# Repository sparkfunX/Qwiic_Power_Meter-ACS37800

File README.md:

SparkX Power Meter - ACS37800 (Qwiic)
===================================================

[*SparkX Power Meter - ACS37800 (Qwiic) (SPX-17873)*](https://www.sparkfun.com/products/17873)

Need a power sensor that can sense voltage up to 60VDC and current up to 30A? This is the product for you!

The Allegro MicroSystems ACS37800 power monitoring IC greatly simplifies the addition of power monitoring to many powered systems and is ideal for
heavy current applications like:
- Monitoring the power drawn by a 3D-printer
- Monitoring the power drawn from a UAV battery
- Battery charging / conditioning
- Solar / photovoltaic panel power monitoring

Allegro’s Hall-effect-based, galvanically isolated current sensing technology achieves reinforced isolation ratings in a small PCB footprint.
These features enable isolated current sensing without expensive Rogowski coils, oversized current transformers, isolated operational amplifiers,
or the power loss of shunt resistors.

The ACS37800 power monitoring IC offers key power measurement parameters that can easily be accessed through its digital interface. Dedicated and
configurable I/O pins for voltage/current zero crossing, undervoltage and overvoltage reporting, and fast overcurrent fault detection are available.
User configuration of the IC is available through on-chip EEPROM.

Important Note
-------------------
This product is not suitable for low current applications due to the +/-0.1A RMS Noise on the current channel.

Sensing less than an Amp? This is _not_ the product for you...

Safety Information
-------------------
**Although the ACS37800 power monitoring IC is capable of monitoring AC power at high line voltages, the SparkX Power Meter is designed for
Safety Extra Low Voltage (SELV) applications of up to 60VDC only. Its use in AC power systems is _not_ recommended.**

Repository Contents
-------------------
* **/Documents** - datasheets etc.
* **/Hardware** - Eagle design files (.brd, .sch)
* **/Production_Test** - production test code (.ino) - run this in the Arduino IDE
* **LICENSE.md** - license information

Documentation
--------------
* **[ACS37800 Arduino Library](https://github.com/sparkfun/SparkFun_ACS37800_Power_Monitor_Arduino_Library)** - Arduino library for the SparkFun Power Meter - ACS37800.
* **[DRAFT Hookup Guide](./HOOKUP.md)** - Basic hookup guide for the SparkX Power Meter - ACS37800.

Product Versions
----------------
* [SPX-17873](https://www.sparkfun.com/products/17873) - Original SparkX Release.

License Information
-------------------

This product is _**open source**_!

Please review the LICENSE.md file for license information.

If you have any questions or concerns on licensing, please contact technical support on our [SparkFun forums](https://forum.sparkfun.com/viewforum.php?f=123).

Distributed as-is; no warranty is given.

- Your friends at SparkFun.

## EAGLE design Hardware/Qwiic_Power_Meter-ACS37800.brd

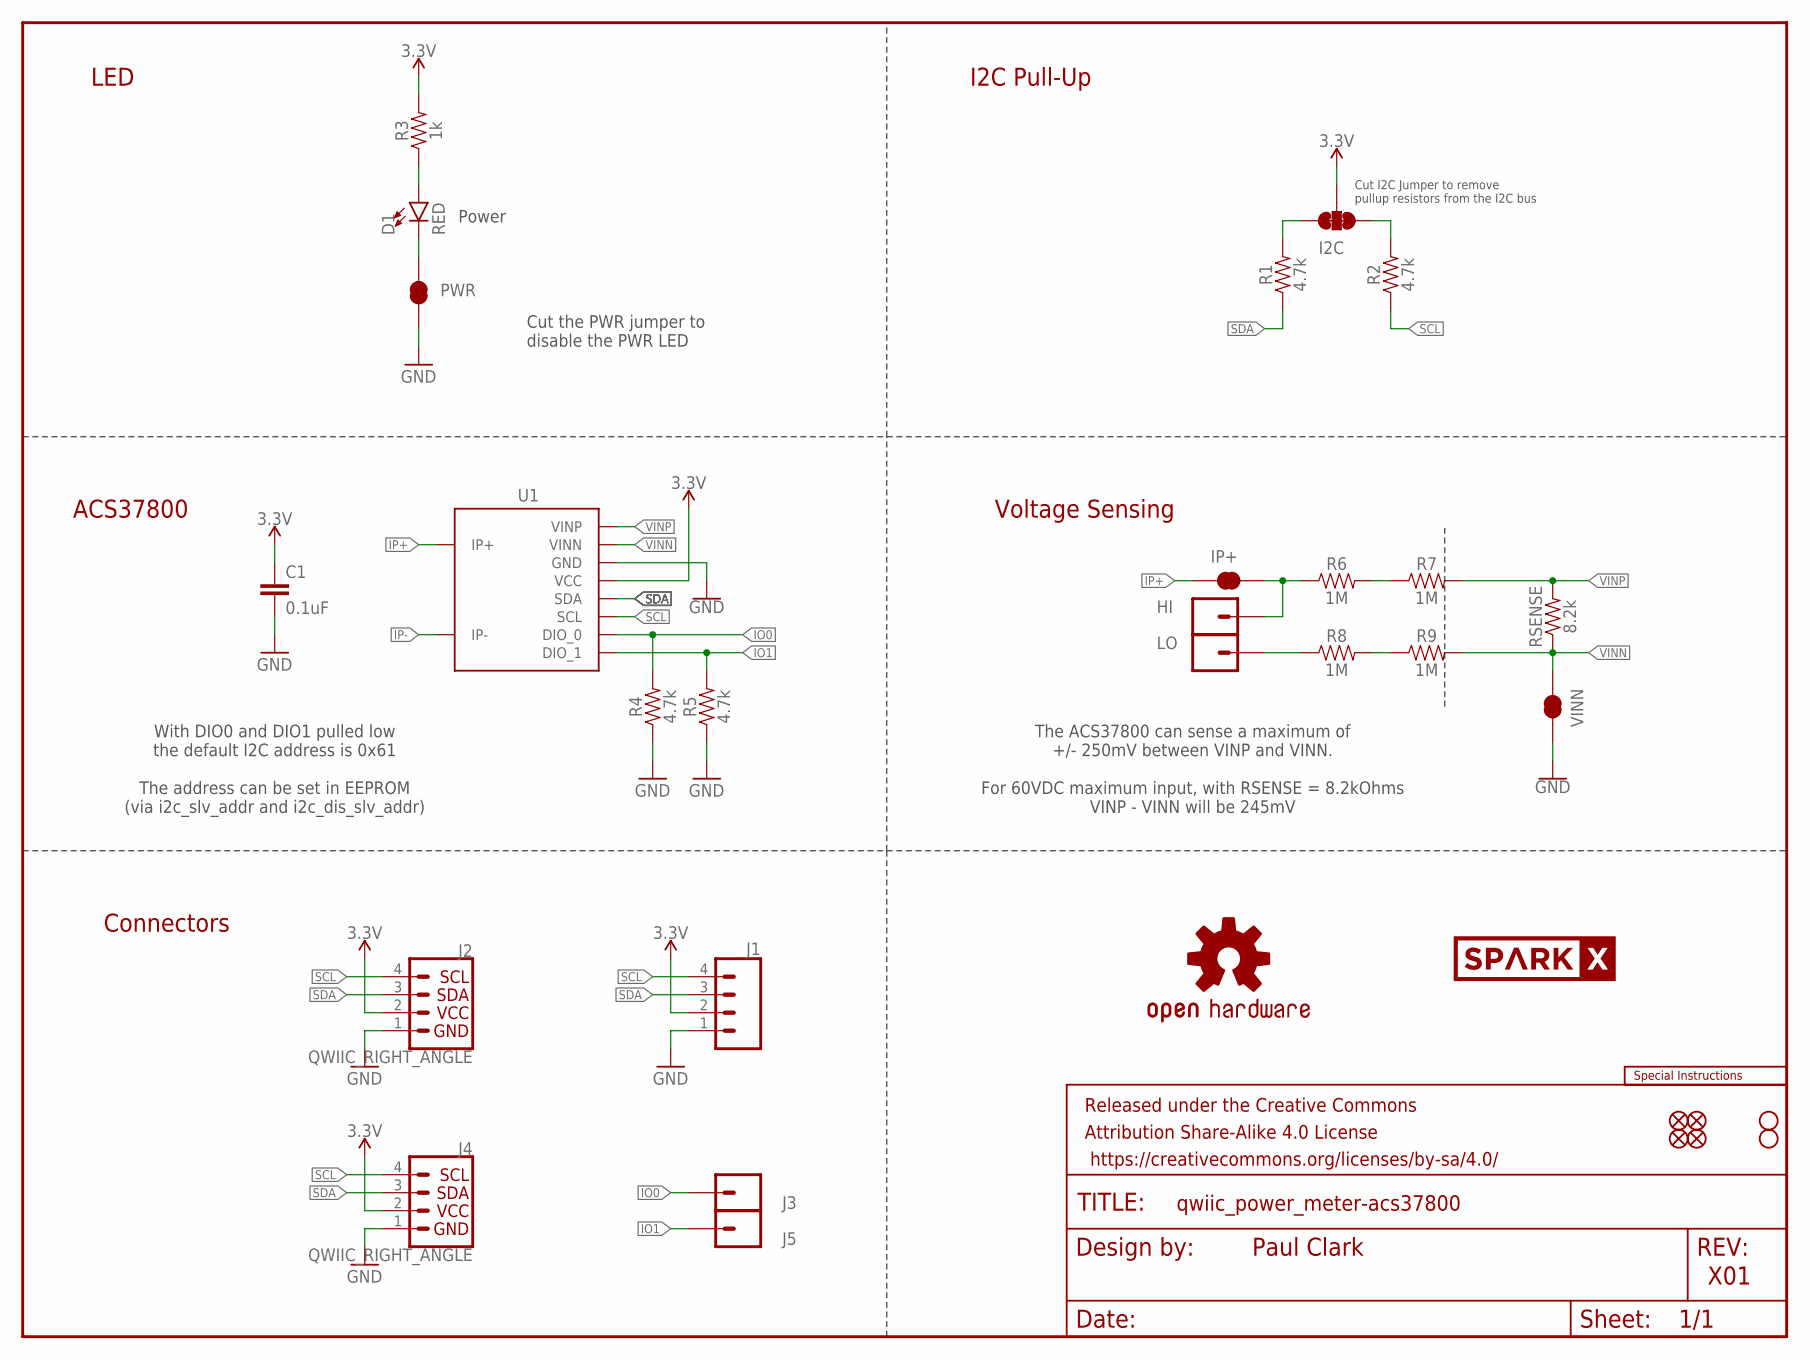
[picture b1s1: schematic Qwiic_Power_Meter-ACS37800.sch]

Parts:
C1: 0.1uF; 0603
D1: RED; LED-0603
FRAME1: FRAME-LETTER; CREATIVE_COMMONS
HI: CONN_01PTH_NO_SILK_YES_STOP; 1X01_NO_SILK
I2C: JUMPER-SMT_3_2-NC_TRACE_SILK; SMT-JUMPER_3_2-NC_TRACE_SILK
IP+: JUMPER-SMT_2_NC_TRACE_SILK; SMT-JUMPER_2_NC_TRACE_SILK
J1: CONN_041X04_NO_SILK; 1X04_NO_SILK
J2, J4: QWIIC_RIGHT_ANGLE; JST04_1MM_RA
J3, J5: CONN_01PTH_NO_SILK_YES_STOP; 1X01_NO_SILK
JP1, JP2, JP5, JP6: FIDUCIALUFIDUCIAL; MICRO-FIDUCIAL
JP3, JP4: STAND-OFF
LO: CONN_01PTH_NO_SILK_YES_STOP; 1X01_NO_SILK
LOGO1: SPECIAL_INSTRUCTIONS-ORDERING; ORDERING_INSTRUCTIONS
LOGO5: OSHW-LOGOS; OSHW-LOGO-S
PWR: JUMPER-SMT_2_NC_TRACE_SILK; SMT-JUMPER_2_NC_TRACE_SILK
R1, R2, R4, R5: 4.7k; 0603
R3: 1k; 0603
R6, R7, R8, R9: 1M; 0603
RSENSE: 8.2k; 0603
U1: ACS37800; ACS37800_THROUGH_HOLE
U$18: SPARKX-LOGO3; SPARKX-SMALL
VINN: JUMPER-SMT_2_NC_TRACE_SILK; SMT-JUMPER_2_NC_TRACE_SILK

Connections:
3.3V: C1.1, I2C.2, J1.2, J2.2, J4.2, R3.2, U1.13 (VCC)
GND: C1.2, J1.1, J2.1, J4.1, PWR.1, R4.1, R5.1, U1.14 (GND), VINN.2
HI: HI.1, IP+.2, R6.1
IO0: J3.1, R4.2, U1.10 (DIO_0)
IO1: J5.1, R5.2, U1.9 (DIO_1)
IP+: IP+.1, U1.1 (IP+), U1.2 (IP+), U1.3 (IP+), U1.4 (IP+), U1.CIN1 (IP+), U1.CIN2 (IP+), U1.CIN3 (IP+), U1.CIN4 (IP+), U1.CIN5 (IP+), U1.CIN6 (IP+), U1.CIN7 (IP+), U1.CIN8 (IP+), U1.CIN9 (IP+), U1.CIN10 (IP+), U1.CIN11 (IP+), U1.CIN12 (IP+), U1.CIN13 (IP+), U1.CIN14 (IP+), U1.CIN15 (IP+), U1.CIN16 (IP+), U1.CIN17 (IP+), U1.CIN18 (IP+), U1.CIN19 (IP+), U1.CIN20 (IP+), U1.CIN21 (IP+), U1.CIN22 (IP+), U1.CIN23 (IP+), U1.CIN24 (IP+), U1.CIN25 (IP+), U1.CIN26 (IP+), U1.CIN27 (IP+), U1.CIN28 (IP+), U1.CIN29 (IP+), U1.CIN30 (IP+), U1.CIN31 (IP+), U1.CIN32 (IP+), U1.CIN33 (IP+), U1.CIN34 (IP+), U1.CIN35 (IP+), U1.CIN36 (IP+), U1.C_IN (IP+), U1.C_IN_BREAKOUT (IP+)
IP-: U1.5 (IP-), U1.6 (IP-), U1.7 (IP-), U1.8 (IP-), U1.COUT1 (IP-), U1.COUT2 (IP-), U1.COUT3 (IP-), U1.COUT4 (IP-), U1.COUT5 (IP-), U1.COUT6 (IP-), U1.COUT7 (IP-), U1.COUT8 (IP-), U1.COUT9 (IP-), U1.COUT10 (IP-), U1.COUT11 (IP-), U1.COUT12 (IP-), U1.COUT13 (IP-), U1.COUT14 (IP-), U1.COUT15 (IP-), U1.COUT16 (IP-), U1.COUT17 (IP-), U1.COUT18 (IP-), U1.COUT19 (IP-), U1.COUT20 (IP-), U1.COUT21 (IP-), U1.COUT22 (IP-), U1.COUT23 (IP-), U1.COUT24 (IP-), U1.COUT25 (IP-), U1.COUT26 (IP-), U1.COUT27 (IP-), U1.COUT28 (IP-), U1.COUT29 (IP-), U1.COUT30 (IP-), U1.COUT31 (IP-), U1.COUT32 (IP-), U1.COUT33 (IP-), U1.COUT34 (IP-), U1.COUT35 (IP-), U1.COUT36 (IP-), U1.C_OUT (IP-), U1.C_OUT_BREAKOUT (IP-)
unnamed: D1.C, PWR.2
unnamed: I2C.3, R1.2
unnamed: D1.A, R3.1
unnamed: I2C.1, R2.2
unnamed: R6.2, R7.1
unnamed: R8.2, R9.1
unnamed: LO.1, R8.1
SCL: J1.4, J2.4, J4.4, R2.1, U1.11 (SCL)
SDA: J1.3, J2.3, J4.3, R1.1, U1.12 (SDA)
VINN: R9.2, RSENSE.1, U1.15 (VINN), VINN.1
VINP: R7.2, RSENSE.2, U1.16 (VINP)

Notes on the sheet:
Paul Clark
X01
Power
I2C Pull-Up
ACS37800
Connectors
Cut the PWR jumper to disable the PWR LED
Cut I2C Jumper to remove pullup resistors from the I2C bus
LED
Voltage Sensing
With DIO0 and DIO1 pulled low the default I2C address is 0x61 The address can be set in EEPROM (via i2c_slv_addr and i2c_dis_slv_addr)
The ACS37800 can sense a maximum of +/- 250mV between VINP and VINN. For 60VDC maximum input, with RSENSE = 8.2kOhms VINP - VINN will be 245mV

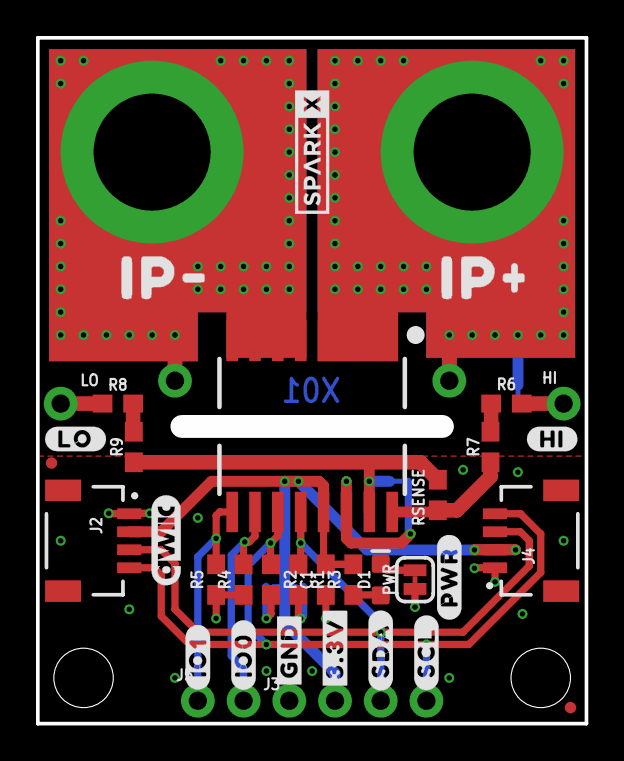
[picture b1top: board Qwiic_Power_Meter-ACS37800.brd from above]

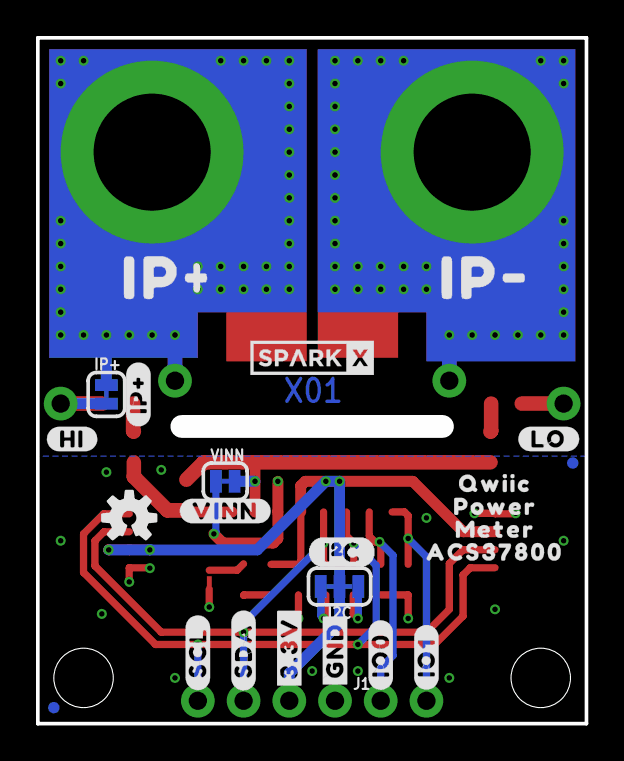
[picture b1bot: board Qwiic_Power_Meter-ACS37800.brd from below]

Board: 4 copper layers, 29.4 x 37.0 mm, 64 parts (25 on the bottom side), 18 nets.

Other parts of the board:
U$1, U$33: #GND#0
U$2, U$34: #3#3V#0
U$3, U$35: #SDA#0
U$4, U$36: #SCL#0
U$5, U$6: #IO0#0
U$7, U$8: #IO1#0
U$9, U$10, U$11, U$12: IP#0
U$13, U$14: #HI#0
U$15: I2C
U$16: QWIIC_5MM
U$17, U$19: #LO#0
U$20: SPARKX-LOGO3; SPARKX-SMALL
U$21: #VINN#0
U$22: #IP##0
U$23: ACS378000
U$24: METER0
U$25: POWER0
U$26: QWIIC0
U$32: #PWR#0

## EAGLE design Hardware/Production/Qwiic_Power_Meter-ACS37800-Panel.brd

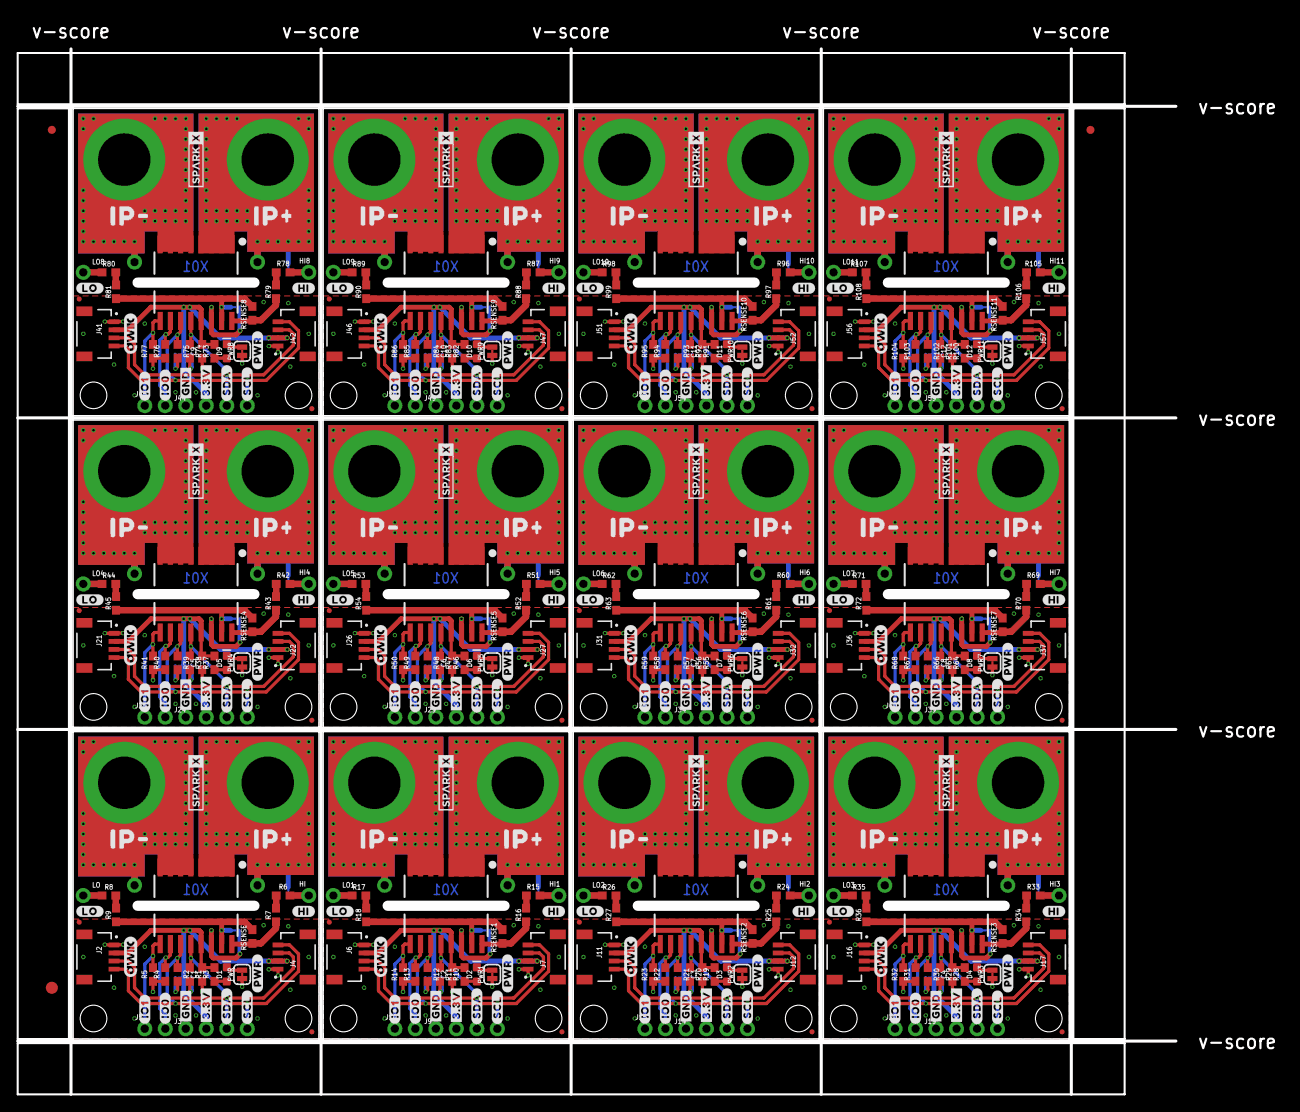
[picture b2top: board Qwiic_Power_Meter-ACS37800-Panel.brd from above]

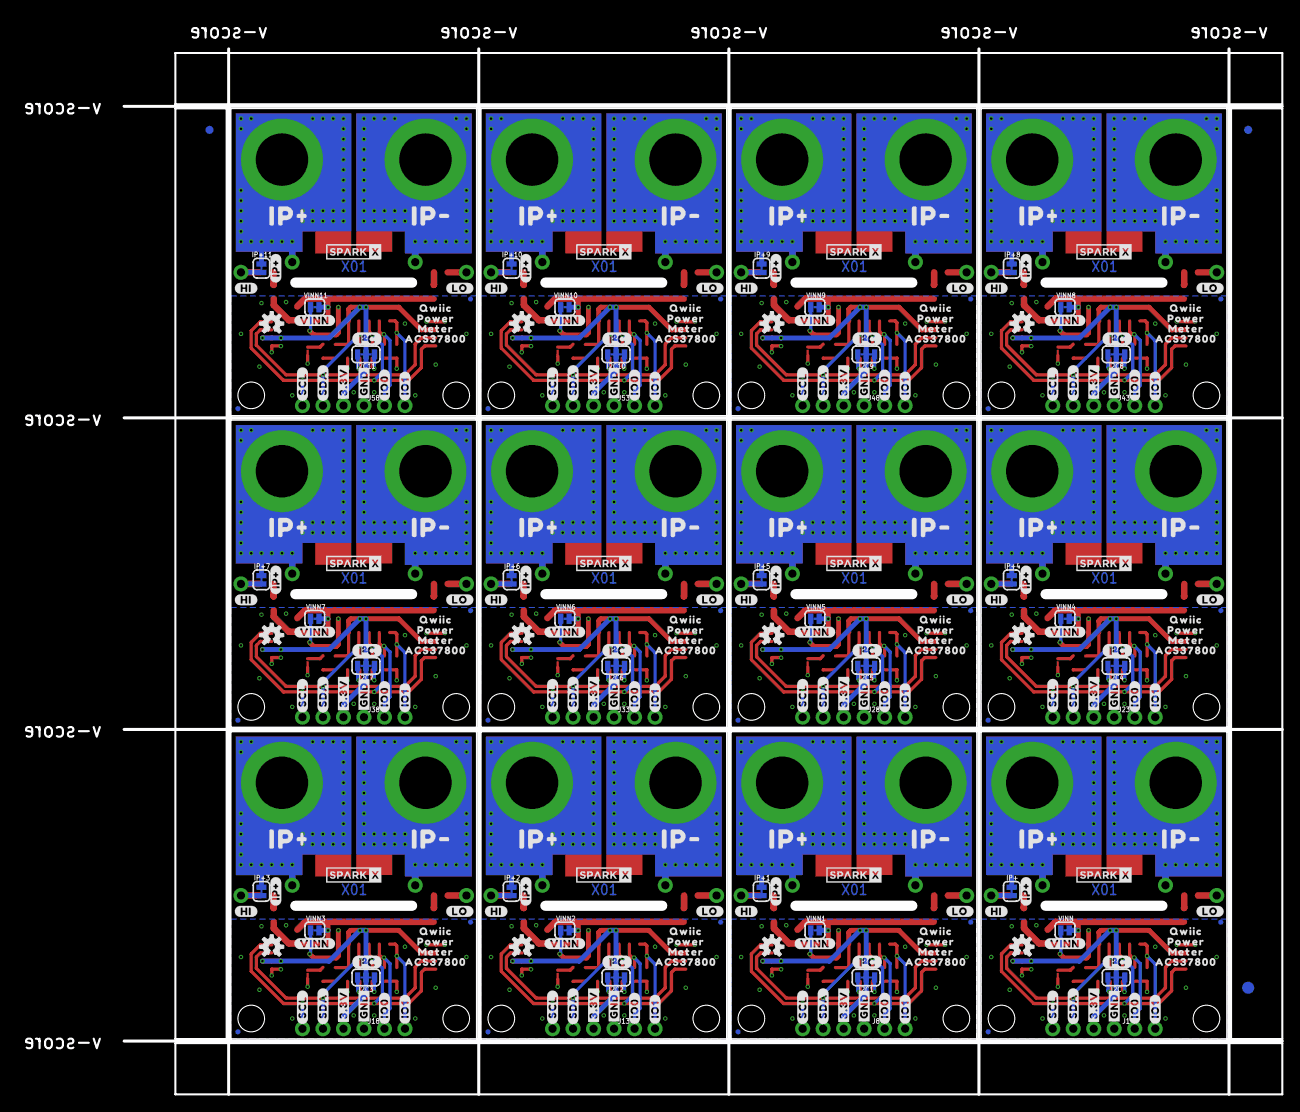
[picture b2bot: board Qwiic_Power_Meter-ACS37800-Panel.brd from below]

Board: 4 copper layers, 155.8 x 132.5 mm, 750 parts (303 on the bottom side), 216 nets.

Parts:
C1, C2, C3, C4, C5, C6, C7, C8, C9, C10, C11, C12: 0.1uF; 0603
D1, D2, D3, D4, D5, D6, D7, D8, D9, D10, D11, D12: RED; LED-0603
E$1, E$2, E$3, E$4: FIDUCIAL-1X2
E$5, E$6: FIDUCIAL-1.5X3
HI, HI1, HI2, HI3, HI4, HI5, HI6, HI7, HI8, HI9, HI10, HI11: 1X01_NO_SILK
I2C, I2C1, I2C2, I2C3, I2C4, I2C5, I2C6, I2C7, I2C8, I2C9, I2C10, I2C11: JUMPER-SMT_3_2-NC_TRACE_SILK; SMT-JUMPER_3_2-NC_TRACE_SILK
IP+, IP+1, IP+2, IP+3, IP+4, IP+5, IP+6, IP+7, IP+8, IP+9, IP+10, IP+11: JUMPER-SMT_2_NC_TRACE_SILK; SMT-JUMPER_2_NC_TRACE_SILK
J1, J8, J13, J18, J23, J28, J33, J38, J43, J48, J53, J58: 1X04_NO_SILK
J2, J4, J6, J7, J11, J12, J16, J17, J21, J22, J26, J27, J31, J32, J36, J37, J41, J42, J46, J47, J51, J52, J56, J57: QWIIC_RIGHT_ANGLE; JST04_1MM_RA
J3, J5, J9, J10, J14, J15, J19, J20, J24, J25, J29, J30, J34, J35, J39, J40, J44, J45, J49, J50, J54, J55, J59, J60: 1X01_NO_SILK
JP1, JP2, JP5, JP6, JP9, JP10, JP11, JP12, JP15, JP16, JP17, JP18, JP21, JP22, JP23, JP24, JP27, JP28, JP29, JP30, JP33, JP34, JP35, JP36, JP39, JP40, JP41, JP42, JP45, JP46, JP47, JP48, JP51, JP52, JP53, JP54, JP57, JP58, JP59, JP60, JP63, JP64, JP65, JP66, JP69, JP70, JP71, JP72: FIDUCIALUFIDUCIAL; MICRO-FIDUCIAL
JP3, JP4, JP7, JP8, JP13, JP14, JP19, JP20, JP25, JP26, JP31, JP32, JP37, JP38, JP43, JP44, JP49, JP50, JP55, JP56, JP61, JP62, JP67, JP68: STAND-OFF
LO, LO1, LO2, LO3, LO4, LO5, LO6, LO7, LO8, LO9, LO10, LO11: 1X01_NO_SILK
LOGO1, LOGO2, LOGO3, LOGO4, LOGO5, LOGO6, LOGO7, LOGO8, LOGO9, LOGO10, LOGO11, LOGO12: OSHW-LOGOS; OSHW-LOGO-S
PWR, PWR1, PWR2, PWR3, PWR4, PWR5, PWR6, PWR7, PWR8, PWR9, PWR10, PWR11: JUMPER-SMT_2_NC_TRACE_SILK; SMT-JUMPER_2_NC_TRACE_SILK
R1, R2, R4, R5, R11, R12, R13, R14, R20, R21, R22, R23, R29, R30, R31, R32, R38, R39, R40, R41, R47, R48, R49, R50, R56, R57, R58, R59, R65, R66, R67, R68, R74, R75, R76, R77, R83, R84, R85, R86, R92, R93, R94, R95, R101, R102, R103, R104: 4.7k; 0603
R3, R10, R19, R28, R37, R46, R55, R64, R73, R82, R91, R100: 1k; 0603
R6, R7, R8, R9, R15, R16, R17, R18, R24, R25, R26, R27, R33, R34, R35, R36, R42, R43, R44, R45, R51, R52, R53, R54, R60, R61, R62, R63, R69, R70, R71, R72, R78, R79, R80, R81, R87, R88, R89, R90, R96, R97, R98, R99, R105, R106, R107, R108: 1M; 0603
RSENSE, RSENSE1, RSENSE2, RSENSE3, RSENSE4, RSENSE5, RSENSE6, RSENSE7, RSENSE8, RSENSE9, RSENSE10, RSENSE11: 8.2k; 0603
U1, U2, U3, U4, U5, U6, U7, U8, U9, U10, U11, U12: ACS37800_THROUGH_HOLE
U$1, U$31, U$33, U$40, U$67, U$71, U$98, U$102, U$129, U$133, U$160, U$164, U$191, U$195, U$222, U$226, U$253, U$257, U$284, U$288, U$315, U$319, U$346, U$350: #GND#0
U$2, U$34, U$37, U$41, U$68, U$72, U$99, U$103, U$130, U$134, U$161, U$165, U$192, U$196, U$223, U$227, U$254, U$258, U$285, U$289, U$316, U$320, U$347, U$351: #3#3V#0
U$3, U$35, U$38, U$42, U$69, U$73, U$100, U$104, U$131, U$135, U$162, U$166, U$193, U$197, U$224, U$228, U$255, U$259, U$286, U$290, U$317, U$321, U$348, U$352: #SDA#0
U$4, U$36, U$39, U$43, U$70, U$74, U$101, U$105, U$132, U$136, U$163, U$167, U$194, U$198, U$225, U$229, U$256, U$260, U$287, U$291, U$318, U$322, U$349, U$353: #SCL#0
U$5, U$6, U$59, U$60, U$90, U$91, U$121, U$122, U$152, U$153, U$183, U$184, U$214, U$215, U$245, U$246, U$276, U$277, U$307, U$308, U$338, U$339, U$369, U$370: #IO0#0
U$7, U$8, U$61, U$62, U$92, U$93, U$123, U$124, U$154, U$155, U$185, U$186, U$216, U$217, U$247, U$248, U$278, U$279, U$309, U$310, U$340, U$341, U$371, U$372: #IO1#0
U$9, U$10, U$11, U$12, U$45, U$46, U$47, U$48, U$76, U$77, U$78, U$79, U$107, U$108, U$109, U$110, U$138, U$139, U$140, U$141, U$169, U$170, U$171, U$172, U$200, U$201, U$202, U$203, U$231, U$232, U$233, U$234, U$262, U$263, U$264, U$265, U$293, U$294, U$295, U$296, U$324, U$325, U$326, U$327, U$355, U$356, U$357, U$358: IP#0
U$13, U$14, U$49, U$50, U$80, U$81, U$111, U$112, U$142, U$143, U$173, U$174, U$204, U$205, U$235, U$236, U$266, U$267, U$297, U$298, U$328, U$329, U$359, U$360: #HI#0
U$15, U$27, U$63, U$94, U$125, U$156, U$187, U$218, U$249, U$280, U$311, U$342: I2C
U$16, U$28, U$64, U$95, U$126, U$157, U$188, U$219, U$250, U$281, U$312, U$343: QWIIC_5MM
U$17, U$19, U$51, U$52, U$82, U$83, U$113, U$114, U$144, U$145, U$175, U$176, U$206, U$207, U$237, U$238, U$268, U$269, U$299, U$300, U$330, U$331, U$361, U$362: #LO#0
U$18, U$20, U$29, U$44, U$65, U$75, U$96, U$106, U$127, U$137, U$158, U$168, U$189, U$199, U$220, U$230, U$251, U$261, U$282, U$292, U$313, U$323, U$344, U$354: SPARKX-LOGO3; SPARKX-SMALL
U$21, U$53, U$84, U$115, U$146, U$177, U$208, U$239, U$270, U$301, U$332, U$363: #VINN#0
U$22, U$54, U$85, U$116, U$147, U$178, U$209, U$240, U$271, U$302, U$333, U$364: #IP##0
U$23, U$55, U$86, U$117, U$148, U$179, U$210, U$241, U$272, U$303, U$334, U$365: ACS378000
U$24, U$56, U$87, U$118, U$149, U$180, U$211, U$242, U$273, U$304, U$335, U$366: METER0
U$25, U$57, U$88, U$119, U$150, U$181, U$212, U$243, U$274, U$305, U$336, U$367: POWER0
U$26, U$58, U$89, U$120, U$151, U$182, U$213, U$244, U$275, U$306, U$337, U$368: QWIIC0
U$30, U$32, U$66, U$97, U$128, U$159, U$190, U$221, U$252, U$283, U$314, U$345: #PWR#0
VINN, VINN1, VINN2, VINN3, VINN4, VINN5, VINN6, VINN7, VINN8, VINN9, VINN10, VINN11: JUMPER-SMT_2_NC_TRACE_SILK; SMT-JUMPER_2_NC_TRACE_SILK

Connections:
3.3V: C1.1, I2C.2, J1.2, J2.2, J4.2, R3.2, U1.13
3.3V1: C2.1, I2C1.2, J6.2, J7.2, J8.2, R10.2, U2.13
3.3V2: C3.1, I2C2.2, J11.2, J12.2, J13.2, R19.2, U3.13
3.3V3: C4.1, I2C3.2, J16.2, J17.2, J18.2, R28.2, U4.13
3.3V4: C5.1, I2C4.2, J21.2, J22.2, J23.2, R37.2, U5.13
3.3V5: C6.1, I2C5.2, J26.2, J27.2, J28.2, R46.2, U6.13
3.3V6: C7.1, I2C6.2, J31.2, J32.2, J33.2, R55.2, U7.13
3.3V7: C8.1, I2C7.2, J36.2, J37.2, J38.2, R64.2, U8.13
3.3V8: C9.1, I2C8.2, J41.2, J42.2, J43.2, R73.2, U9.13
3.3V9: C10.1, I2C9.2, J46.2, J47.2, J48.2, R82.2, U10.13
3.3V10: C11.1, I2C10.2, J51.2, J52.2, J53.2, R91.2, U11.13
3.3V11: C12.1, I2C11.2, J56.2, J57.2, J58.2, R100.2, U12.13
GND: C1.2, J1.1, J2.1, J4.1, PWR.1, R4.1, R5.1, U1.14, VINN.2
GND1: C2.2, J6.1, J7.1, J8.1, PWR1.1, R13.1, R14.1, U2.14, VINN1.2
GND2: C3.2, J11.1, J12.1, J13.1, PWR2.1, R22.1, R23.1, U3.14, VINN2.2
GND3: C4.2, J16.1, J17.1, J18.1, PWR3.1, R31.1, R32.1, U4.14, VINN3.2
GND4: C5.2, J21.1, J22.1, J23.1, PWR4.1, R40.1, R41.1, U5.14, VINN4.2
GND5: C6.2, J26.1, J27.1, J28.1, PWR5.1, R49.1, R50.1, U6.14, VINN5.2
GND6: C7.2, J31.1, J32.1, J33.1, PWR6.1, R58.1, R59.1, U7.14, VINN6.2
GND7: C8.2, J36.1, J37.1, J38.1, PWR7.1, R67.1, R68.1, U8.14, VINN7.2
GND8: C9.2, J41.1, J42.1, J43.1, PWR8.1, R76.1, R77.1, U9.14, VINN8.2
GND9: C10.2, J46.1, J47.1, J48.1, PWR9.1, R85.1, R86.1, U10.14, VINN9.2
GND10: C11.2, J51.1, J52.1, J53.1, PWR10.1, R94.1, R95.1, U11.14, VINN10.2
GND11: C12.2, J56.1, J57.1, J58.1, PWR11.1, R103.1, R104.1, U12.14, VINN11.2
HI: HI.1, IP+.2, R6.1
HI1: HI1.1, IP+1.2, R15.1
HI2: HI2.1, IP+2.2, R24.1
HI3: HI3.1, IP+3.2, R33.1
HI4: HI4.1, IP+4.2, R42.1
HI5: HI5.1, IP+5.2, R51.1
HI6: HI6.1, IP+6.2, R60.1
HI7: HI7.1, IP+7.2, R69.1
HI8: HI8.1, IP+8.2, R78.1
HI9: HI9.1, IP+9.2, R87.1
HI10: HI10.1, IP+10.2, R96.1
HI11: HI11.1, IP+11.2, R105.1
IO0: J3.1, R4.2, U1.10
IO1: J5.1, R5.2, U1.9
IO2: J9.1, R13.2, U2.10
IO3: J10.1, R14.2, U2.9
IO4: J14.1, R22.2, U3.10
IO5: J15.1, R23.2, U3.9
IO6: J19.1, R31.2, U4.10
IO7: J20.1, R32.2, U4.9
IO8: J24.1, R40.2, U5.10
IO9: J25.1, R41.2, U5.9
IO10: J29.1, R49.2, U6.10
IO11: J30.1, R50.2, U6.9
IO12: J34.1, R58.2, U7.10
IO13: J35.1, R59.2, U7.9
IO14: J39.1, R67.2, U8.10
IO15: J40.1, R68.2, U8.9
IO16: J44.1, R76.2, U9.10
IO17: J45.1, R77.2, U9.9
IO18: J49.1, R85.2, U10.10
IO19: J50.1, R86.2, U10.9
IO20: J54.1, R94.2, U11.10
IO21: J55.1, R95.2, U11.9
IO22: J59.1, R103.2, U12.10
IO23: J60.1, R104.2, U12.9
IP+: IP+.1, U1.1, U1.2, U1.3, U1.4, U1.CIN1, U1.CIN2, U1.CIN3, U1.CIN4, U1.CIN5, U1.CIN6, U1.CIN7, U1.CIN8, U1.CIN9, U1.CIN10, U1.CIN11, U1.CIN12, U1.CIN13, U1.CIN14, U1.CIN15, U1.CIN16, U1.CIN17, U1.CIN18, U1.CIN19, U1.CIN20, U1.CIN21, U1.CIN22, U1.CIN23, U1.CIN24, U1.CIN25, U1.CIN26, U1.CIN27, U1.CIN28, U1.CIN29, U1.CIN30, U1.CIN31, U1.CIN32, U1.CIN33, U1.CIN34, U1.CIN35, U1.CIN36, U1.C_IN, U1.C_IN_BREAKOUT
IP+1: IP+1.1, U2.1, U2.2, U2.3, U2.4, U2.CIN1, U2.CIN2, U2.CIN3, U2.CIN4, U2.CIN5, U2.CIN6, U2.CIN7, U2.CIN8, U2.CIN9, U2.CIN10, U2.CIN11, U2.CIN12, U2.CIN13, U2.CIN14, U2.CIN15, U2.CIN16, U2.CIN17, U2.CIN18, U2.CIN19, U2.CIN20, U2.CIN21, U2.CIN22, U2.CIN23, U2.CIN24, U2.CIN25, U2.CIN26, U2.CIN27, U2.CIN28, U2.CIN29, U2.CIN30, U2.CIN31, U2.CIN32, U2.CIN33, U2.CIN34, U2.CIN35, U2.CIN36, U2.C_IN, U2.C_IN_BREAKOUT
IP+2: IP+2.1, U3.1, U3.2, U3.3, U3.4, U3.CIN1, U3.CIN2, U3.CIN3, U3.CIN4, U3.CIN5, U3.CIN6, U3.CIN7, U3.CIN8, U3.CIN9, U3.CIN10, U3.CIN11, U3.CIN12, U3.CIN13, U3.CIN14, U3.CIN15, U3.CIN16, U3.CIN17, U3.CIN18, U3.CIN19, U3.CIN20, U3.CIN21, U3.CIN22, U3.CIN23, U3.CIN24, U3.CIN25, U3.CIN26, U3.CIN27, U3.CIN28, U3.CIN29, U3.CIN30, U3.CIN31, U3.CIN32, U3.CIN33, U3.CIN34, U3.CIN35, U3.CIN36, U3.C_IN, U3.C_IN_BREAKOUT
IP+3: IP+3.1, U4.1, U4.2, U4.3, U4.4, U4.CIN1, U4.CIN2, U4.CIN3, U4.CIN4, U4.CIN5, U4.CIN6, U4.CIN7, U4.CIN8, U4.CIN9, U4.CIN10, U4.CIN11, U4.CIN12, U4.CIN13, U4.CIN14, U4.CIN15, U4.CIN16, U4.CIN17, U4.CIN18, U4.CIN19, U4.CIN20, U4.CIN21, U4.CIN22, U4.CIN23, U4.CIN24, U4.CIN25, U4.CIN26, U4.CIN27, U4.CIN28, U4.CIN29, U4.CIN30, U4.CIN31, U4.CIN32, U4.CIN33, U4.CIN34, U4.CIN35, U4.CIN36, U4.C_IN, U4.C_IN_BREAKOUT
IP+4: IP+4.1, U5.1, U5.2, U5.3, U5.4, U5.CIN1, U5.CIN2, U5.CIN3, U5.CIN4, U5.CIN5, U5.CIN6, U5.CIN7, U5.CIN8, U5.CIN9, U5.CIN10, U5.CIN11, U5.CIN12, U5.CIN13, U5.CIN14, U5.CIN15, U5.CIN16, U5.CIN17, U5.CIN18, U5.CIN19, U5.CIN20, U5.CIN21, U5.CIN22, U5.CIN23, U5.CIN24, U5.CIN25, U5.CIN26, U5.CIN27, U5.CIN28, U5.CIN29, U5.CIN30, U5.CIN31, U5.CIN32, U5.CIN33, U5.CIN34, U5.CIN35, U5.CIN36, U5.C_IN, U5.C_IN_BREAKOUT
IP+5: IP+5.1, U6.1, U6.2, U6.3, U6.4, U6.CIN1, U6.CIN2, U6.CIN3, U6.CIN4, U6.CIN5, U6.CIN6, U6.CIN7, U6.CIN8, U6.CIN9, U6.CIN10, U6.CIN11, U6.CIN12, U6.CIN13, U6.CIN14, U6.CIN15, U6.CIN16, U6.CIN17, U6.CIN18, U6.CIN19, U6.CIN20, U6.CIN21, U6.CIN22, U6.CIN23, U6.CIN24, U6.CIN25, U6.CIN26, U6.CIN27, U6.CIN28, U6.CIN29, U6.CIN30, U6.CIN31, U6.CIN32, U6.CIN33, U6.CIN34, U6.CIN35, U6.CIN36, U6.C_IN, U6.C_IN_BREAKOUT
IP+6: IP+6.1, U7.1, U7.2, U7.3, U7.4, U7.CIN1, U7.CIN2, U7.CIN3, U7.CIN4, U7.CIN5, U7.CIN6, U7.CIN7, U7.CIN8, U7.CIN9, U7.CIN10, U7.CIN11, U7.CIN12, U7.CIN13, U7.CIN14, U7.CIN15, U7.CIN16, U7.CIN17, U7.CIN18, U7.CIN19, U7.CIN20, U7.CIN21, U7.CIN22, U7.CIN23, U7.CIN24, U7.CIN25, U7.CIN26, U7.CIN27, U7.CIN28, U7.CIN29, U7.CIN30, U7.CIN31, U7.CIN32, U7.CIN33, U7.CIN34, U7.CIN35, U7.CIN36, U7.C_IN, U7.C_IN_BREAKOUT
IP+7: IP+7.1, U8.1, U8.2, U8.3, U8.4, U8.CIN1, U8.CIN2, U8.CIN3, U8.CIN4, U8.CIN5, U8.CIN6, U8.CIN7, U8.CIN8, U8.CIN9, U8.CIN10, U8.CIN11, U8.CIN12, U8.CIN13, U8.CIN14, U8.CIN15, U8.CIN16, U8.CIN17, U8.CIN18, U8.CIN19, U8.CIN20, U8.CIN21, U8.CIN22, U8.CIN23, U8.CIN24, U8.CIN25, U8.CIN26, U8.CIN27, U8.CIN28, U8.CIN29, U8.CIN30, U8.CIN31, U8.CIN32, U8.CIN33, U8.CIN34, U8.CIN35, U8.CIN36, U8.C_IN, U8.C_IN_BREAKOUT
IP+8: IP+8.1, U9.1, U9.2, U9.3, U9.4, U9.CIN1, U9.CIN2, U9.CIN3, U9.CIN4, U9.CIN5, U9.CIN6, U9.CIN7, U9.CIN8, U9.CIN9, U9.CIN10, U9.CIN11, U9.CIN12, U9.CIN13, U9.CIN14, U9.CIN15, U9.CIN16, U9.CIN17, U9.CIN18, U9.CIN19, U9.CIN20, U9.CIN21, U9.CIN22, U9.CIN23, U9.CIN24, U9.CIN25, U9.CIN26, U9.CIN27, U9.CIN28, U9.CIN29, U9.CIN30, U9.CIN31, U9.CIN32, U9.CIN33, U9.CIN34, U9.CIN35, U9.CIN36, U9.C_IN, U9.C_IN_BREAKOUT
IP+9: IP+9.1, U10.1, U10.2, U10.3, U10.4, U10.CIN1, U10.CIN2, U10.CIN3, U10.CIN4, U10.CIN5, U10.CIN6, U10.CIN7, U10.CIN8, U10.CIN9, U10.CIN10, U10.CIN11, U10.CIN12, U10.CIN13, U10.CIN14, U10.CIN15, U10.CIN16, U10.CIN17, U10.CIN18, U10.CIN19, U10.CIN20, U10.CIN21, U10.CIN22, U10.CIN23, U10.CIN24, U10.CIN25, U10.CIN26, U10.CIN27, U10.CIN28, U10.CIN29, U10.CIN30, U10.CIN31, U10.CIN32, U10.CIN33, U10.CIN34, U10.CIN35, U10.CIN36, U10.C_IN, U10.C_IN_BREAKOUT
IP+10: IP+10.1, U11.1, U11.2, U11.3, U11.4, U11.CIN1, U11.CIN2, U11.CIN3, U11.CIN4, U11.CIN5, U11.CIN6, U11.CIN7, U11.CIN8, U11.CIN9, U11.CIN10, U11.CIN11, U11.CIN12, U11.CIN13, U11.CIN14, U11.CIN15, U11.CIN16, U11.CIN17, U11.CIN18, U11.CIN19, U11.CIN20, U11.CIN21, U11.CIN22, U11.CIN23, U11.CIN24, U11.CIN25, U11.CIN26, U11.CIN27, U11.CIN28, U11.CIN29, U11.CIN30, U11.CIN31, U11.CIN32, U11.CIN33, U11.CIN34, U11.CIN35, U11.CIN36, U11.C_IN, U11.C_IN_BREAKOUT
IP+11: IP+11.1, U12.1, U12.2, U12.3, U12.4, U12.CIN1, U12.CIN2, U12.CIN3, U12.CIN4, U12.CIN5, U12.CIN6, U12.CIN7, U12.CIN8, U12.CIN9, U12.CIN10, U12.CIN11, U12.CIN12, U12.CIN13, U12.CIN14, U12.CIN15, U12.CIN16, U12.CIN17, U12.CIN18, U12.CIN19, U12.CIN20, U12.CIN21, U12.CIN22, U12.CIN23, U12.CIN24, U12.CIN25, U12.CIN26, U12.CIN27, U12.CIN28, U12.CIN29, U12.CIN30, U12.CIN31, U12.CIN32, U12.CIN33, U12.CIN34, U12.CIN35, U12.CIN36, U12.C_IN, U12.C_IN_BREAKOUT
IP-: U1.5, U1.6, U1.7, U1.8, U1.COUT1, U1.COUT2, U1.COUT3, U1.COUT4, U1.COUT5, U1.COUT6, U1.COUT7, U1.COUT8, U1.COUT9, U1.COUT10, U1.COUT11, U1.COUT12, U1.COUT13, U1.COUT14, U1.COUT15, U1.COUT16, U1.COUT17, U1.COUT18, U1.COUT19, U1.COUT20, U1.COUT21, U1.COUT22, U1.COUT23, U1.COUT24, U1.COUT25, U1.COUT26, U1.COUT27, U1.COUT28, U1.COUT29, U1.COUT30, U1.COUT31, U1.COUT32, U1.COUT33, U1.COUT34, U1.COUT35, U1.COUT36, U1.C_OUT, U1.C_OUT_BREAKOUT
IP-1: U2.5, U2.6, U2.7, U2.8, U2.COUT1, U2.COUT2, U2.COUT3, U2.COUT4, U2.COUT5, U2.COUT6, U2.COUT7, U2.COUT8, U2.COUT9, U2.COUT10, U2.COUT11, U2.COUT12, U2.COUT13, U2.COUT14, U2.COUT15, U2.COUT16, U2.COUT17, U2.COUT18, U2.COUT19, U2.COUT20, U2.COUT21, U2.COUT22, U2.COUT23, U2.COUT24, U2.COUT25, U2.COUT26, U2.COUT27, U2.COUT28, U2.COUT29, U2.COUT30, U2.COUT31, U2.COUT32, U2.COUT33, U2.COUT34, U2.COUT35, U2.COUT36, U2.C_OUT, U2.C_OUT_BREAKOUT
IP-2: U3.5, U3.6, U3.7, U3.8, U3.COUT1, U3.COUT2, U3.COUT3, U3.COUT4, U3.COUT5, U3.COUT6, U3.COUT7, U3.COUT8, U3.COUT9, U3.COUT10, U3.COUT11, U3.COUT12, U3.COUT13, U3.COUT14, U3.COUT15, U3.COUT16, U3.COUT17, U3.COUT18, U3.COUT19, U3.COUT20, U3.COUT21, U3.COUT22, U3.COUT23, U3.COUT24, U3.COUT25, U3.COUT26, U3.COUT27, U3.COUT28, U3.COUT29, U3.COUT30, U3.COUT31, U3.COUT32, U3.COUT33, U3.COUT34, U3.COUT35, U3.COUT36, U3.C_OUT, U3.C_OUT_BREAKOUT
IP-3: U4.5, U4.6, U4.7, U4.8, U4.COUT1, U4.COUT2, U4.COUT3, U4.COUT4, U4.COUT5, U4.COUT6, U4.COUT7, U4.COUT8, U4.COUT9, U4.COUT10, U4.COUT11, U4.COUT12, U4.COUT13, U4.COUT14, U4.COUT15, U4.COUT16, U4.COUT17, U4.COUT18, U4.COUT19, U4.COUT20, U4.COUT21, U4.COUT22, U4.COUT23, U4.COUT24, U4.COUT25, U4.COUT26, U4.COUT27, U4.COUT28, U4.COUT29, U4.COUT30, U4.COUT31, U4.COUT32, U4.COUT33, U4.COUT34, U4.COUT35, U4.COUT36, U4.C_OUT, U4.C_OUT_BREAKOUT
IP-4: U5.5, U5.6, U5.7, U5.8, U5.COUT1, U5.COUT2, U5.COUT3, U5.COUT4, U5.COUT5, U5.COUT6, U5.COUT7, U5.COUT8, U5.COUT9, U5.COUT10, U5.COUT11, U5.COUT12, U5.COUT13, U5.COUT14, U5.COUT15, U5.COUT16, U5.COUT17, U5.COUT18, U5.COUT19, U5.COUT20, U5.COUT21, U5.COUT22, U5.COUT23, U5.COUT24, U5.COUT25, U5.COUT26, U5.COUT27, U5.COUT28, U5.COUT29, U5.COUT30, U5.COUT31, U5.COUT32, U5.COUT33, U5.COUT34, U5.COUT35, U5.COUT36, U5.C_OUT, U5.C_OUT_BREAKOUT
IP-5: U6.5, U6.6, U6.7, U6.8, U6.COUT1, U6.COUT2, U6.COUT3, U6.COUT4, U6.COUT5, U6.COUT6, U6.COUT7, U6.COUT8, U6.COUT9, U6.COUT10, U6.COUT11, U6.COUT12, U6.COUT13, U6.COUT14, U6.COUT15, U6.COUT16, U6.COUT17, U6.COUT18, U6.COUT19, U6.COUT20, U6.COUT21, U6.COUT22, U6.COUT23, U6.COUT24, U6.COUT25, U6.COUT26, U6.COUT27, U6.COUT28, U6.COUT29, U6.COUT30, U6.COUT31, U6.COUT32, U6.COUT33, U6.COUT34, U6.COUT35, U6.COUT36, U6.C_OUT, U6.C_OUT_BREAKOUT
IP-6: U7.5, U7.6, U7.7, U7.8, U7.COUT1, U7.COUT2, U7.COUT3, U7.COUT4, U7.COUT5, U7.COUT6, U7.COUT7, U7.COUT8, U7.COUT9, U7.COUT10, U7.COUT11, U7.COUT12, U7.COUT13, U7.COUT14, U7.COUT15, U7.COUT16, U7.COUT17, U7.COUT18, U7.COUT19, U7.COUT20, U7.COUT21, U7.COUT22, U7.COUT23, U7.COUT24, U7.COUT25, U7.COUT26, U7.COUT27, U7.COUT28, U7.COUT29, U7.COUT30, U7.COUT31, U7.COUT32, U7.COUT33, U7.COUT34, U7.COUT35, U7.COUT36, U7.C_OUT, U7.C_OUT_BREAKOUT
IP-7: U8.5, U8.6, U8.7, U8.8, U8.COUT1, U8.COUT2, U8.COUT3, U8.COUT4, U8.COUT5, U8.COUT6, U8.COUT7, U8.COUT8, U8.COUT9, U8.COUT10, U8.COUT11, U8.COUT12, U8.COUT13, U8.COUT14, U8.COUT15, U8.COUT16, U8.COUT17, U8.COUT18, U8.COUT19, U8.COUT20, U8.COUT21, U8.COUT22, U8.COUT23, U8.COUT24, U8.COUT25, U8.COUT26, U8.COUT27, U8.COUT28, U8.COUT29, U8.COUT30, U8.COUT31, U8.COUT32, U8.COUT33, U8.COUT34, U8.COUT35, U8.COUT36, U8.C_OUT, U8.C_OUT_BREAKOUT
IP-8: U9.5, U9.6, U9.7, U9.8, U9.COUT1, U9.COUT2, U9.COUT3, U9.COUT4, U9.COUT5, U9.COUT6, U9.COUT7, U9.COUT8, U9.COUT9, U9.COUT10, U9.COUT11, U9.COUT12, U9.COUT13, U9.COUT14, U9.COUT15, U9.COUT16, U9.COUT17, U9.COUT18, U9.COUT19, U9.COUT20, U9.COUT21, U9.COUT22, U9.COUT23, U9.COUT24, U9.COUT25, U9.COUT26, U9.COUT27, U9.COUT28, U9.COUT29, U9.COUT30, U9.COUT31, U9.COUT32, U9.COUT33, U9.COUT34, U9.COUT35, U9.COUT36, U9.C_OUT, U9.C_OUT_BREAKOUT
IP-9: U10.5, U10.6, U10.7, U10.8, U10.COUT1, U10.COUT2, U10.COUT3, U10.COUT4, U10.COUT5, U10.COUT6, U10.COUT7, U10.COUT8, U10.COUT9, U10.COUT10, U10.COUT11, U10.COUT12, U10.COUT13, U10.COUT14, U10.COUT15, U10.COUT16, U10.COUT17, U10.COUT18, U10.COUT19, U10.COUT20, U10.COUT21, U10.COUT22, U10.COUT23, U10.COUT24, U10.COUT25, U10.COUT26, U10.COUT27, U10.COUT28, U10.COUT29, U10.COUT30, U10.COUT31, U10.COUT32, U10.COUT33, U10.COUT34, U10.COUT35, U10.COUT36, U10.C_OUT, U10.C_OUT_BREAKOUT
IP-10: U11.5, U11.6, U11.7, U11.8, U11.COUT1, U11.COUT2, U11.COUT3, U11.COUT4, U11.COUT5, U11.COUT6, U11.COUT7, U11.COUT8, U11.COUT9, U11.COUT10, U11.COUT11, U11.COUT12, U11.COUT13, U11.COUT14, U11.COUT15, U11.COUT16, U11.COUT17, U11.COUT18, U11.COUT19, U11.COUT20, U11.COUT21, U11.COUT22, U11.COUT23, U11.COUT24, U11.COUT25, U11.COUT26, U11.COUT27, U11.COUT28, U11.COUT29, U11.COUT30, U11.COUT31, U11.COUT32, U11.COUT33, U11.COUT34, U11.COUT35, U11.COUT36, U11.C_OUT, U11.C_OUT_BREAKOUT
IP-11: U12.5, U12.6, U12.7, U12.8, U12.COUT1, U12.COUT2, U12.COUT3, U12.COUT4, U12.COUT5, U12.COUT6, U12.COUT7, U12.COUT8, U12.COUT9, U12.COUT10, U12.COUT11, U12.COUT12, U12.COUT13, U12.COUT14, U12.COUT15, U12.COUT16, U12.COUT17, U12.COUT18, U12.COUT19, U12.COUT20, U12.COUT21, U12.COUT22, U12.COUT23, U12.COUT24, U12.COUT25, U12.COUT26, U12.COUT27, U12.COUT28, U12.COUT29, U12.COUT30, U12.COUT31, U12.COUT32, U12.COUT33, U12.COUT34, U12.COUT35, U12.COUT36, U12.C_OUT, U12.C_OUT_BREAKOUT
unnamed: D1.C, PWR.2
unnamed: I2C.3, R1.2
unnamed: D1.A, R3.1
unnamed: I2C.1, R2.2
unnamed: R6.2, R7.1
unnamed: R8.2, R9.1
unnamed: D2.A, R10.1
unnamed: LO.1, R8.1
unnamed: I2C1.3, R11.2
unnamed: I2C1.1, R12.2
unnamed: R15.2, R16.1
unnamed: R17.2, R18.1
unnamed: LO1.1, R17.1
unnamed: D2.C, PWR1.2
unnamed: D3.A, R19.1
unnamed: I2C2.3, R20.2
unnamed: I2C2.1, R21.2
unnamed: R24.2, R25.1
unnamed: R26.2, R27.1
unnamed: LO2.1, R26.1
unnamed: D3.C, PWR2.2
unnamed: D4.A, R28.1
unnamed: I2C3.3, R29.2
unnamed: I2C3.1, R30.2
unnamed: R33.2, R34.1
unnamed: R35.2, R36.1
unnamed: LO3.1, R35.1
unnamed: D4.C, PWR3.2
unnamed: D5.A, R37.1
unnamed: I2C4.3, R38.2
unnamed: I2C4.1, R39.2
unnamed: R42.2, R43.1
unnamed: R44.2, R45.1
unnamed: LO4.1, R44.1
unnamed: D5.C, PWR4.2
unnamed: D6.A, R46.1
unnamed: I2C5.3, R47.2
unnamed: I2C5.1, R48.2
unnamed: R51.2, R52.1
unnamed: R53.2, R54.1
unnamed: LO5.1, R53.1
unnamed: D6.C, PWR5.2
unnamed: D7.A, R55.1
unnamed: I2C6.3, R56.2
unnamed: I2C6.1, R57.2
unnamed: R60.2, R61.1
unnamed: R62.2, R63.1
unnamed: LO6.1, R62.1
unnamed: D7.C, PWR6.2
unnamed: D8.A, R64.1
unnamed: I2C7.3, R65.2
unnamed: I2C7.1, R66.2
unnamed: R69.2, R70.1
unnamed: R71.2, R72.1
unnamed: LO7.1, R71.1
unnamed: D8.C, PWR7.2
unnamed: D9.A, R73.1
unnamed: I2C8.3, R74.2
unnamed: I2C8.1, R75.2
unnamed: R78.2, R79.1
unnamed: R80.2, R81.1
unnamed: LO8.1, R80.1
unnamed: D9.C, PWR8.2
unnamed: D10.A, R82.1
unnamed: I2C9.3, R83.2
unnamed: I2C9.1, R84.2
unnamed: R87.2, R88.1
unnamed: R89.2, R90.1
unnamed: LO9.1, R89.1
unnamed: D10.C, PWR9.2
unnamed: D11.A, R91.1
unnamed: I2C10.3, R92.2
unnamed: I2C10.1, R93.2
unnamed: R96.2, R97.1
unnamed: R98.2, R99.1
unnamed: LO10.1, R98.1
unnamed: D11.C, PWR10.2
unnamed: D12.A, R100.1
unnamed: I2C11.3, R101.2
unnamed: I2C11.1, R102.2
unnamed: R105.2, R106.1
unnamed: R107.2, R108.1
unnamed: LO11.1, R107.1
unnamed: D12.C, PWR11.2
SCL: J1.4, J2.4, J4.4, R2.1, U1.11
SCL1: J6.4, J7.4, J8.4, R12.1, U2.11
SCL2: J11.4, J12.4, J13.4, R21.1, U3.11
SCL3: J16.4, J17.4, J18.4, R30.1, U4.11
SCL4: J21.4, J22.4, J23.4, R39.1, U5.11
SCL5: J26.4, J27.4, J28.4, R48.1, U6.11
SCL6: J31.4, J32.4, J33.4, R57.1, U7.11
SCL7: J36.4, J37.4, J38.4, R66.1, U8.11
SCL8: J41.4, J42.4, J43.4, R75.1, U9.11
SCL9: J46.4, J47.4, J48.4, R84.1, U10.11
SCL10: J51.4, J52.4, J53.4, R93.1, U11.11
SCL11: J56.4, J57.4, J58.4, R102.1, U12.11
SDA: J1.3, J2.3, J4.3, R1.1, U1.12
SDA1: J6.3, J7.3, J8.3, R11.1, U2.12
SDA2: J11.3, J12.3, J13.3, R20.1, U3.12
SDA3: J16.3, J17.3, J18.3, R29.1, U4.12
SDA4: J21.3, J22.3, J23.3, R38.1, U5.12
SDA5: J26.3, J27.3, J28.3, R47.1, U6.12
SDA6: J31.3, J32.3, J33.3, R56.1, U7.12
SDA7: J36.3, J37.3, J38.3, R65.1, U8.12
SDA8: J41.3, J42.3, J43.3, R74.1, U9.12
SDA9: J46.3, J47.3, J48.3, R83.1, U10.12
SDA10: J51.3, J52.3, J53.3, R92.1, U11.12
SDA11: J56.3, J57.3, J58.3, R101.1, U12.12
VINN: R9.2, RSENSE.1, U1.15, VINN.1
VINN1: R18.2, RSENSE1.1, U2.15, VINN1.1
VINN2: R27.2, RSENSE2.1, U3.15, VINN2.1
VINN3: R36.2, RSENSE3.1, U4.15, VINN3.1
VINN4: R45.2, RSENSE4.1, U5.15, VINN4.1
VINN5: R54.2, RSENSE5.1, U6.15, VINN5.1
VINN6: R63.2, RSENSE6.1, U7.15, VINN6.1
VINN7: R72.2, RSENSE7.1, U8.15, VINN7.1
VINN8: R81.2, RSENSE8.1, U9.15, VINN8.1
VINN9: R90.2, RSENSE9.1, U10.15, VINN9.1
VINN10: R99.2, RSENSE10.1, U11.15, VINN10.1
VINN11: R108.2, RSENSE11.1, U12.15, VINN11.1
VINP: R7.2, RSENSE.2, U1.16
VINP1: R16.2, RSENSE1.2, U2.16
VINP2: R25.2, RSENSE2.2, U3.16
VINP3: R34.2, RSENSE3.2, U4.16
VINP4: R43.2, RSENSE4.2, U5.16
VINP5: R52.2, RSENSE5.2, U6.16
VINP6: R61.2, RSENSE6.2, U7.16
VINP7: R70.2, RSENSE7.2, U8.16
VINP8: R79.2, RSENSE8.2, U9.16
VINP9: R88.2, RSENSE9.2, U10.16
VINP10: R97.2, RSENSE10.2, U11.16
VINP11: R106.2, RSENSE11.2, U12.16

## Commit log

2021-01-22 Adding the SKU and new PROD_ID
2021-03-15 Update default I2C address on schematic
2021-03-19 Adding production test code (.ino)
2021-04-17 Add product image
2021-04-23 Add DRAFT hook-up guide
2022-01-10 Update Production_Test.ino - crs_sns is not always 5

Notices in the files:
parts and their libraries:
SparkFun-Resistors: Licensing: Creative Commons ShareAlike 4.0 International - https://creativecommons.org/licenses/by-sa/4.0
SparkFun-Aesthetics: Released under the Creative Commons Attribution Share-Alike 4.0 License
SparkFun-Aesthetics: https://creativecommons.org/licenses/by-sa/4.0
